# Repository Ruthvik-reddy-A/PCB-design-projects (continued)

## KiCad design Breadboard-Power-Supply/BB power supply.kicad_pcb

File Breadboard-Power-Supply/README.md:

# ⚡ Breadboard Power Supply

A compact, dual-voltage regulated power supply module designed specifically to power circuits on a breadboard. This project provides reliable 3.3V and 5V outputs and is ideal for prototyping and electronics education.

---

## 📸 Preview

---

## ⚙️ Features

- ✅ Provides both **3.3V** and **5V** outputs
- 🔌 Accepts input from USB or DC barrel jack (6V–12V)
- 🧰 Onboard voltage regulators (e.g., AMS1117)
- 📎 Designed to plug directly into standard breadboards
- 🔋 On/Off toggle switches for each rail
- 🧲 Polarity protection and status LEDs included

---

## 🔧 Circuit Overview

This power module uses two linear regulators (AMS1117 or similar) to deliver stable voltages for breadboard circuits. It includes onboard:

- Input power jack (DC barrel or USB micro-B)
- Two low-dropout regulators: one for 3.3V, one for 5V
- Slide switches for enabling/disabling each voltage rail
- Pin headers to mount directly on a breadboard
- Power indicator LEDs

---

## 📋 Bill of Materials (BOM)

| Component | Value / Part       | Description                         |
|-----------|--------------------|-------------------------------------|
| U1        | AMS1117-5.0        | 5V Linear Regulator                 |
| U2        | AMS1117-3.3        | 3.3V Linear Regulator               |
| D1        | 1N4007             | Input polarity protection diode     |
| C1, C2    | 10µF Electrolytic  | Input/output filter capacitors      |
| R1, R2    | 330Ω               | LED current-limiting resistors      |
| LED1, LED2| Red/Green LEDs     | Power indicators                    |
| SW1, SW2  | SPDT Slide Switch  | ON/OFF control for 5V/3.3V rails     |
| J1        | DC Barrel Jack     | Power input                         |
| J2        | USB (optional)     | Alternate power input               |
| Header    | Male Pin Header    | Breadboard pins                     |

---

## 🛠️ Assembly & Usage

1. **Solder all components** as per the PCB layout.
2. Insert the module into a breadboard.
3. Connect 6–12V input via USB or barrel jack.
4. Use the toggle switches to activate 5V or 3.3V output rails.
5. Verify voltages with a multimeter before connecting sensitive components.

---

## 📦 Folder Structure

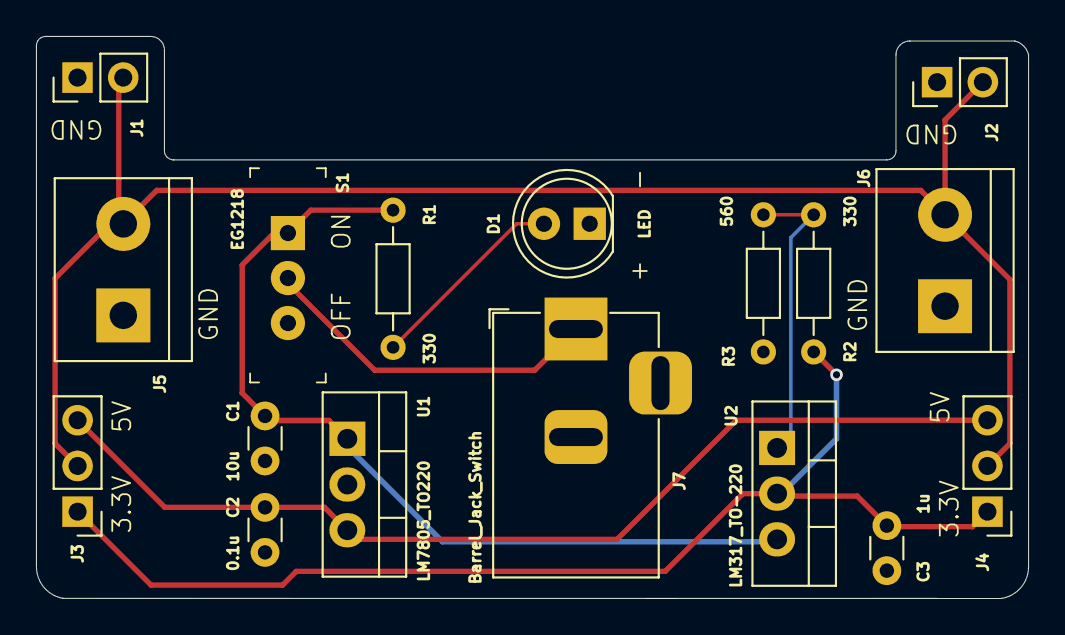
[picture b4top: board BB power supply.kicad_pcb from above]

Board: 2 copper layers, 55.1 x 31.2 mm, 17 parts (0 on the bottom side), 8 nets.

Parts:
C1: 10u; C_Disc_D3.0mm_W1.6mm_P2.50mm
C2: 0.1u; C_Disc_D3.0mm_W1.6mm_P2.50mm
C3: 1u; C_Disc_D3.0mm_W1.6mm_P2.50mm
D1: LED; LED_D5.0mm
J1, J2: Conn_01x02_Pin; PinHeader_1x02_P2.54mm_Vertical
J3, J4: Conn_01x03_Pin; PinHeader_1x03_P2.54mm_Vertical
J5, J6: Screw_Terminal_01x02; TerminalBlock_bornier-2_P5.08mm
J7: Barrel_Jack_Switch; BarrelJack_Horizontal
R1, R2: 330; R_Axial_DIN0204_L3.6mm_D1.6mm_P7.62mm_Horizontal
R3: 560; R_Axial_DIN0204_L3.6mm_D1.6mm_P7.62mm_Horizontal
S1: EG1218; Switch_Slide_11.6x4mm_EG1218
U1: LM7805_TO220; TO-220-3_Vertical
U2: LM317_TO-220; TO-220-3_Vertical

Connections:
/3.3V: C3.1, J3.1, J4.1, R2.2, U2.2 (VO)
/5V: C2.1, J3.3, J4.3, U1.3 (VO)
/12V: C1.1, R1.2, S1.1, U1.1 (VI), U2.3 (VI)
/PWR_input: J7.1, S1.2
/PWR_output: J1.2, J2.2, J3.2, J4.2, J5.2, J6.2
GND: C1.2, C2.2, C3.2, D1.1 (K), J1.1, J2.1, J5.1, J6.1, J7.2, J7.3, R3.1, U1.2 (GND)
unnamed: D1.2 (A), R1.1
unnamed: R2.1, R3.2, U2.1 (ADJ)

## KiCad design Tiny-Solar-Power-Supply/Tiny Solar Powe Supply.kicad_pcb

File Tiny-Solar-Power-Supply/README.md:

# ☀️ Tiny Solar Power Supply

A minimalist, solar-powered **boost converter** circuit that charges a single 1.2V NiMH AA battery and provides a regulated **3.3V output**, ideal for microcontrollers or low-power IoT devices.

Originally published in Elektor Magazine, this design is adapted to fit into small enclosures like salvaged solar garden lights. It balances simplicity, efficiency, and practicality for real-world solar energy harvesting.

---

## 📸 Preview

<!-- Replace with actual image path -->

---

## ⚙️ Key Features

- 🔋 Charges a 1.2V NiMH AA cell via small solar panel
- ⚡ Boosts battery voltage to regulated **3.3V output**
- ⛔ Auto-disables output when panel is exposed to light (configurable)
- 🔄 Optional manual On/Off jumper
- 📦 Small, easy-to-assemble PCB — fits inside common garden light enclosures

---

## 🔧 Technical Details

- **Controller IC**: AP3015 (Micropower DC-DC Boost Converter)
- **Input**: 1V–1.2V (NiMH battery)
- **Output**: ~3.3V regulated (via R1/R2 voltage divider)
- **Max Output Current**:  
  - 100 mA with AP3015A  
  - 350 mA with AP3015
- **Battery Charging**: Solar panel through Schottky diode (SS14)
- **Shutdown Logic**: Uses 2N7002 MOSFET to disable output when sunlight is present

---

## 📋 Bill of Materials (BOM)

| Component | Value / Part       | Description                         |
|-----------|--------------------|-------------------------------------|
| IC1       | AP3015 / AP3015A   | Boost Converter IC                  |
| L1        | 10 µH              | Inductor, 680 mA (resistor-style OK)|
| D1, D2    | SS14               | Schottky diodes                     |
| T1        | 2N7002             | MOSFET for shutdown control         |
| R1, R4    | 1 MΩ               | Feedback + gate pull-down resistors |
| R2        | 604 kΩ             | Voltage divider (sets 3.3V)         |
| R3        | 10 kΩ              | Gate resistor                       |
| C1        | 4.7 µF, 50V X7R    | Input cap                           |
| C2        | 22 µF, 10V X7R     | Output smoothing cap                |
| C3        | 10 pF              | FB stability cap                    |
| K1–K4     | 2-pin headers      | Battery, solar input, jumper, output|

---

## 🖥️ Schematic & Working Principle

- **Daytime**: Sunlight charges the NiMH battery via D2 and disables the converter via T1.
- **Night**: T1 turns off, enabling IC1 to boost the battery to 3.3V.
- **Optional**: Skip T1 to have always-on output or control with jumper at K3.

 <!-- Replace with your schematic -->

---

## 🚀 Usage Notes

1. Connect a small solar panel (3–6V open circuit) to `K4`.
2. Insert a 1.2V NiMH AA cell to `K2`.
3. Regulated 3.3V will be available at `K1` when solar input drops.
4. Use jumper or switch on `K3` to override automatic shutdown.

---

---

## 🔗 Reference

- 📰 Original article: [Elektor Labs – Tiny Solar Supply](https://elektormagazine.com/labs/tiny-solar-supply)
- 📄 AP3015 Datasheet: [Diodes Inc](https://www.diodes.com/assets/Datasheets/AP3015.pdf)

---

## 📄 License

This project is open-source under the [MIT License](../LICENSE).  
All design adaptations credited to the Elektor Lab article by Clemens Valens.

---

## 🙋‍♂️ Author & Contact

Designed and adapted by **Ruthvik Reddy A**  
📩 Email: `reddy.ruthvik0411@gmail.com`

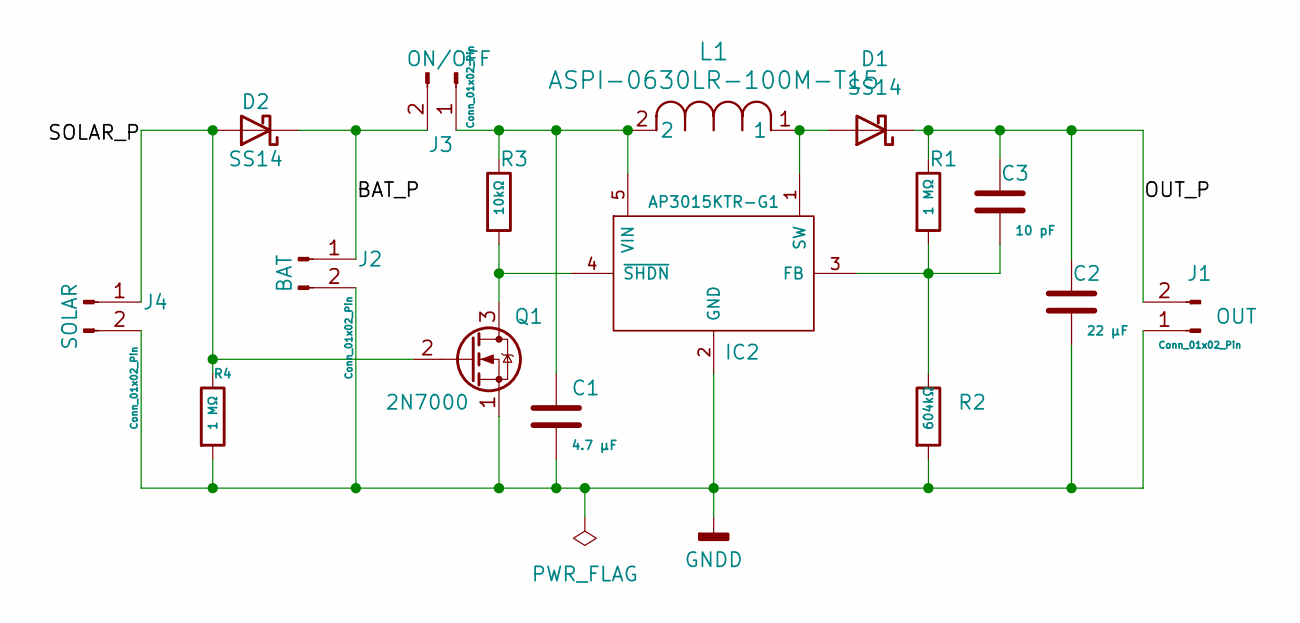
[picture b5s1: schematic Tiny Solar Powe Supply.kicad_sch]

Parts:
C1: 4.7 μF; C_0805_2012Metric
C2: 22 μF; C_1206_3216Metric
C3: 10 pF; C_0805_2012Metric
D1, D2: SS14; D_SMA
IC2: AP3015KTR-G1; SOT95P280X145-5N; Mouser Part Number 621-AP3015KTR-G1
J1, J2, J3: Conn_01x02_Pin; PinHeader_1x02_P2.54mm_Vertical
J4: Conn_01x02_Pin; PinHeader_1x02_P2.00mm_Horizontal
L1: ASPI-0630LR-100M-T15; IND_ASPI-0630LR_ABR
Q1: 2N7000; TO-92_Inline
R1, R4: 1 MΩ; R_0805_2012Metric
R2: 604kΩ; R_0805_2012Metric
R3: 10kΩ; R_0805_2012Metric

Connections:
/BAT_P: D2.1 (K), J2.1, J3.2
/OUT_P: C2.1, C3.1, D1.1 (K), J1.2, R1.1
/SOLAR_P: D2.2 (A), J4.1, Q1.2 (G), R4.1
GNDD: C1.2, C2.2, IC2.2 (GND), J1.1, J2.2, J4.2, Q1.1 (S), R2.2, R4.2
unnamed: D1.2 (A), IC2.1 (SW), L1.1
unnamed: C3.2, IC2.3 (FB), R1.2, R2.1
unnamed: C1.1, IC2.5 (VIN), J3.1, L1.2, R3.1
unnamed: IC2.4 (~SHDN), Q1.3 (D), R3.2

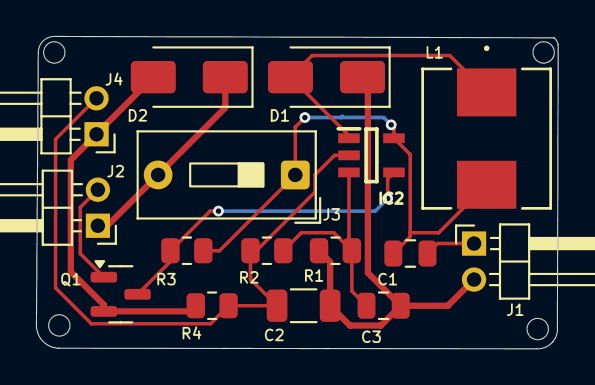
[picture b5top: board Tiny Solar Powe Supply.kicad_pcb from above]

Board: 2 copper layers, 29.0 x 17.4 mm, 16 parts (0 on the bottom side), 8 nets.

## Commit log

2025-06-12 📦 Added 3 PCB projects as subfolders, including all files (.gitignore, README.md, etc.)
2025-06-12 Rename README.md to README.md
2025-06-12 Completed Project
2025-06-12 Added files to LED Torch project
2025-06-12 Added files for Project 1 - LED Torch
2025-06-13 Added Guide
2025-06-13 Completed project & Updated
2025-06-23 Add circuit, schematic, and firmware for GPS + GSM Tracker with EEPROM logging
2025-06-23 Added gitignore
2025-06-24 Completed Pcb design
